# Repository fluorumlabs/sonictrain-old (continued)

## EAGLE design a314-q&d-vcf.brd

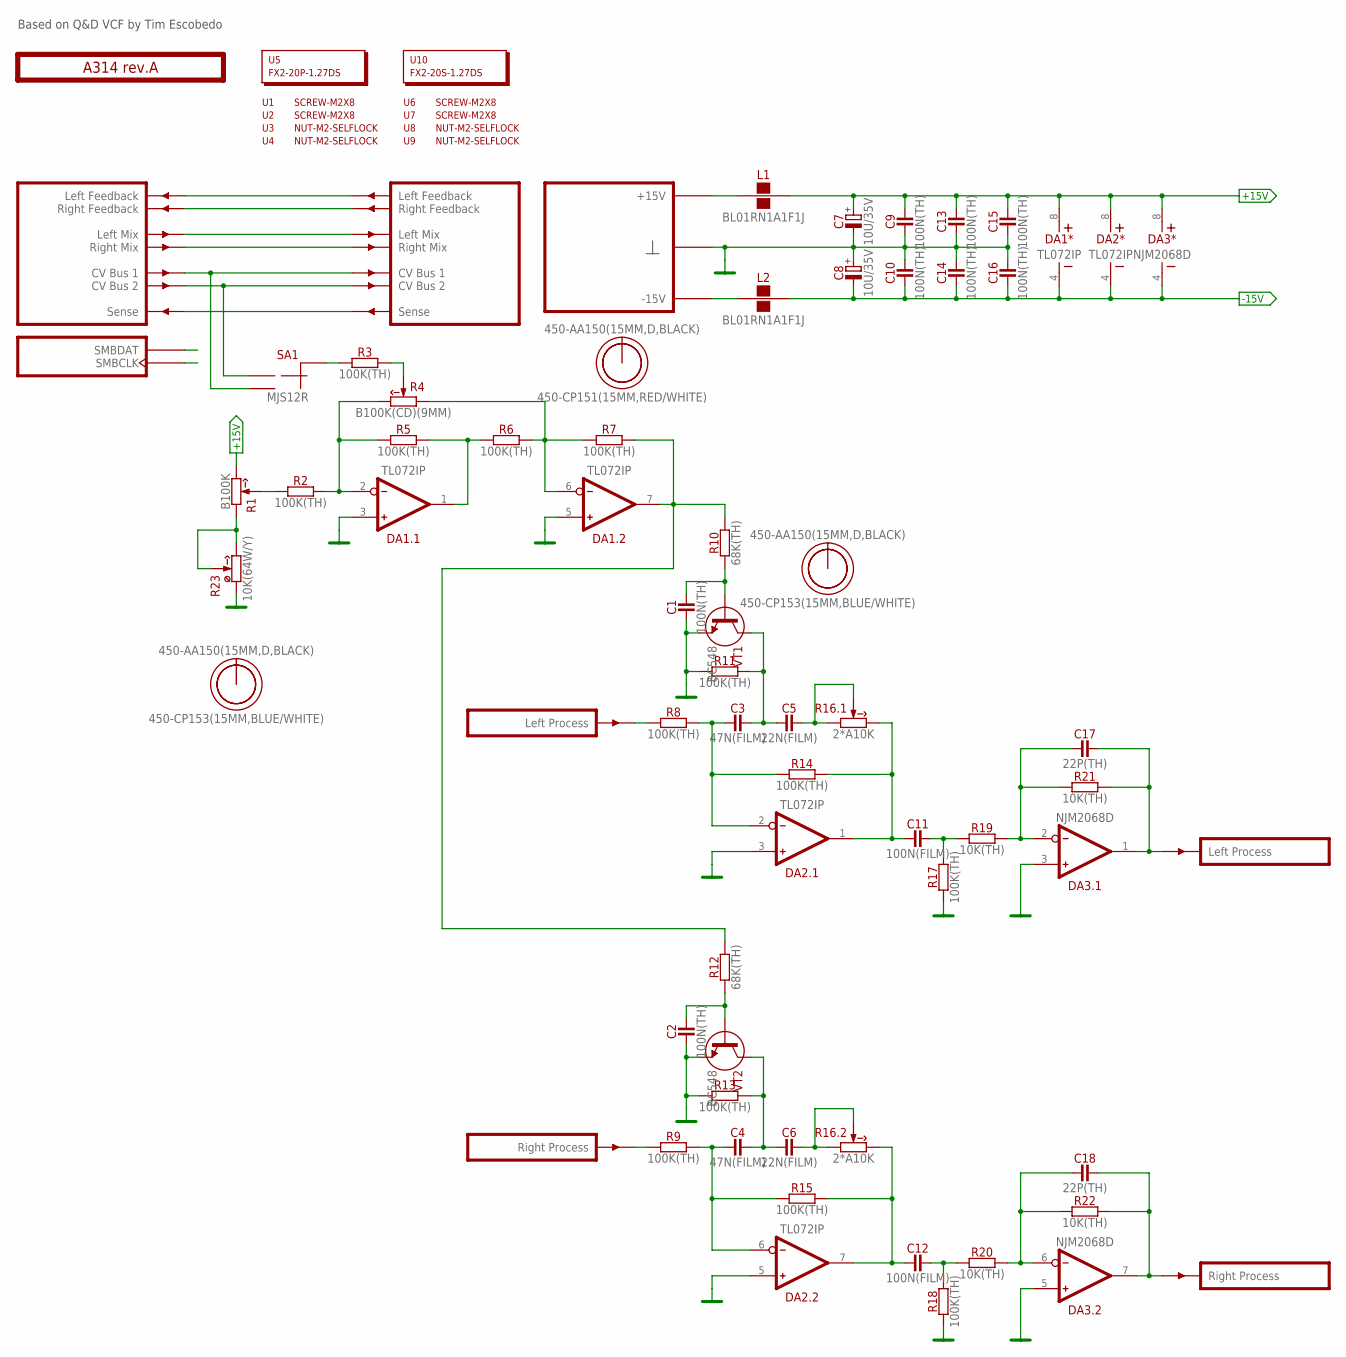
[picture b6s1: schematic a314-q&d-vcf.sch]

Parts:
C1, C2, C9, C10, C13, C14, C15, C16: 100N(TH); C050-024X044
C3, C4: 47N(FILM); C050-025X075
C5, C6: 22N(FILM); C050-025X075
C7, C8: 10U/35V; E2-5
C11, C12: 100N(FILM); C050-025X075
C17, C18: 22P(TH); C050-024X044
DA1, DA2: TL072IP; DIP-8
DA3: NJM2068D; DIP-8
L1, L2: BL01RN1A1F1J; BL01RN1A
O1, O2, O3: 450-AA150(15MM,D,BLACK); EMPTY
O4: 450-CP151(15MM,RED/WHITE); EMPTY
O5, O6: 450-CP153(15MM,BLUE/WHITE); EMPTY
PCB1: A314 rev.A; ST2-BOARD-50
R1: B100K; RV11-SINGLE
R2, R3, R5, R6, R7, R8, R9, R11, R13, R14, R15, R17, R18: 100K(TH); R-0207/10
R4: B100K(CD)(9MM); RV09-SINGLE
R10, R12: 68K(TH); R-0207/10
R16: 2*A10K; RV11-DUAL
R19, R20, R21, R22: 10K(TH); R-0207/10
R23: 10K(64W/Y); 64W
SA1: MJS12R; APEM-MJS12R
U1, U2, U6, U7: SCREW-M2X8; EMPTY
U3, U4, U8, U9: NUT-M2-SELFLOCK; EMPTY
U5: FX2-20P-1.27DS; EMPTY
U10: FX2-20S-1.27DS; EMPTY
VT1, VT2: BC548; TO92

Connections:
+15V: C7.+, C9.2, C13.2, C15.2, DA1.8 (V+), DA2.8 (V+), DA3.8 (V+), L1.2, R1.3 (CW)
-15V: C8.-, C10.1, C14.1, C16.1, DA1.4 (V-), DA2.4 (V-), DA3.4 (V-), L2.2
GND: C1.1, C2.1, C7.-, C8.+, C9.1, C10.2, C13.1, C14.2, C15.1, C16.2, DA1.3 (IN+), DA1.5 (IN+), DA2.3 (IN+), DA2.5 (IN+), DA3.3 (IN+), DA3.5 (IN+), PCB1.B4 (GND), PCB1.B4' (GND), PCB1.B5 (GND), PCB1.B5' (GND), PCB1.B6 (GND), PCB1.B6' (GND), PCB1.B7 (GND), PCB1.B7' (GND), PCB1.B8 (GND), PCB1.B8' (GND), R11.1, R13.1, R17.1, R18.1, R23.1 (CCW), VT1.3 (E), VT2.3 (E)
LMIX: PCB1.ALMIX (LMIX), PCB1.ALMIX' (LMIX')
unnamed: L1.1, PCB1.A+15 (P+15V), PCB1.A+15' (P+15V), PCB1.B+15 (P+15V), PCB1.B+15' (P+15V)
unnamed: PCB1.ALFBK (LFBK), PCB1.ALFBK' (LFBK')
unnamed: R3.2, R4.2 (W)
unnamed: PCB1.ARFBK (RFBK), PCB1.ARFBK' (RFBK')
unnamed: DA1.2 (IN-), R2.2, R4.3 (CW), R5.1
unnamed: DA1.1 (OUT), R5.2, R6.1
unnamed: DA1.6 (IN-), R4.1 (CCW), R6.2, R7.1
unnamed: C18.1, DA3.6 (IN-), R20.2, R22.1
unnamed: R3.1, SA1.C (CM)
unnamed: C4.1, DA2.6 (IN-), R9.2, R15.1
unnamed: C3.1, DA2.2 (IN-), R8.2, R14.1
unnamed: PCB1.BINL (INL), R8.1
unnamed: R1.2 (W), R2.1
unnamed: C11.1, DA2.1 (OUT), R14.2, R16.3 (CW)
unnamed: PCB1.ACV1 (CV1), PCB1.ACV1' (CV1'), SA1.NO (2)
unnamed: PCB1.BSENSE (SENSE), PCB1.BSENSE' (SENSE')
unnamed: C11.2, R17.2, R19.1
unnamed: C12.1, DA2.7 (OUT), R15.2, R16.3' (CW)
unnamed: C5.2, R16.1 (CCW), R16.2 (W)
unnamed: C12.2, R18.2, R20.1
unnamed: C6.2, R16.1' (CCW), R16.2' (W)
unnamed: C3.2, C5.1, R11.2, VT1.1 (C)
unnamed: C1.2, R10.1, VT1.2 (B)
unnamed: C4.2, C6.1, R13.2, VT2.1 (C)
unnamed: L2.1, PCB1.A-15 (P-15V), PCB1.A-15' (P-15V), PCB1.B-15 (P-15V), PCB1.B-15' (P-15V)
unnamed: C2.2, R12.1, VT2.2 (B)
unnamed: PCB1.BINR (INR), R9.1
unnamed: DA1.7 (OUT), R7.2, R10.2, R12.2
unnamed: C18.2, DA3.7 (OUT), PCB1.BOUTR' (OUTR), R22.2
unnamed: C17.1, DA3.2 (IN-), R19.2, R21.1
unnamed: C17.2, DA3.1 (OUT), PCB1.BOUTL' (OUTL), R21.2
unnamed: R1.1 (CCW), R23.3 (CW), R23.S (W), R23.S@1 (W)
unnamed: PCB1.ASMBDAT (SMBDAT), PCB1.ASMBDAT' (SMBDAT)
unnamed: PCB1.ACV2 (CV2), PCB1.ACV2' (CV2'), SA1.NC (1)
unnamed: PCB1.ASMBCLK (SMBCLK), PCB1.ASMBCLK' (SMBCLK)
RMIX: PCB1.ARMIX (RMIX), PCB1.ARMIX' (RMIX')

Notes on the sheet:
Based on Q&D VCF by Tim Escobedo

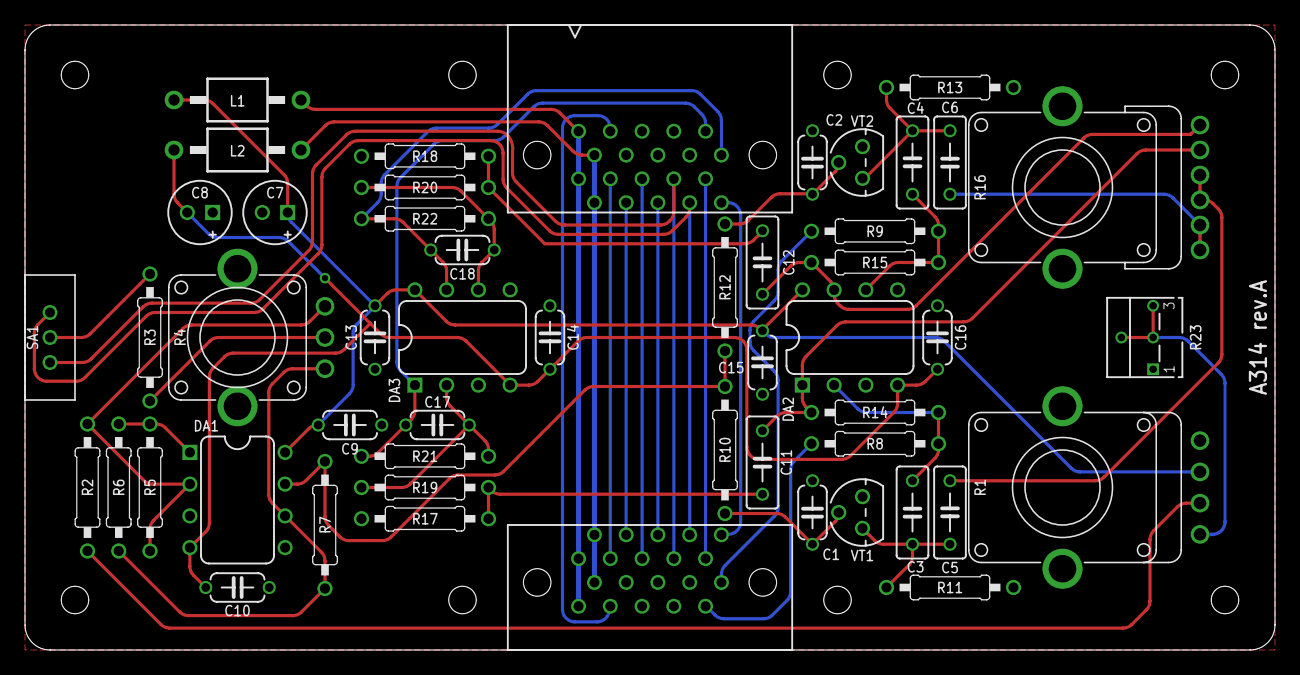
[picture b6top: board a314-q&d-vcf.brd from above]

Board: 2 copper layers, 100.0 x 50.0 mm, 66 parts (0 on the bottom side), 40 nets.

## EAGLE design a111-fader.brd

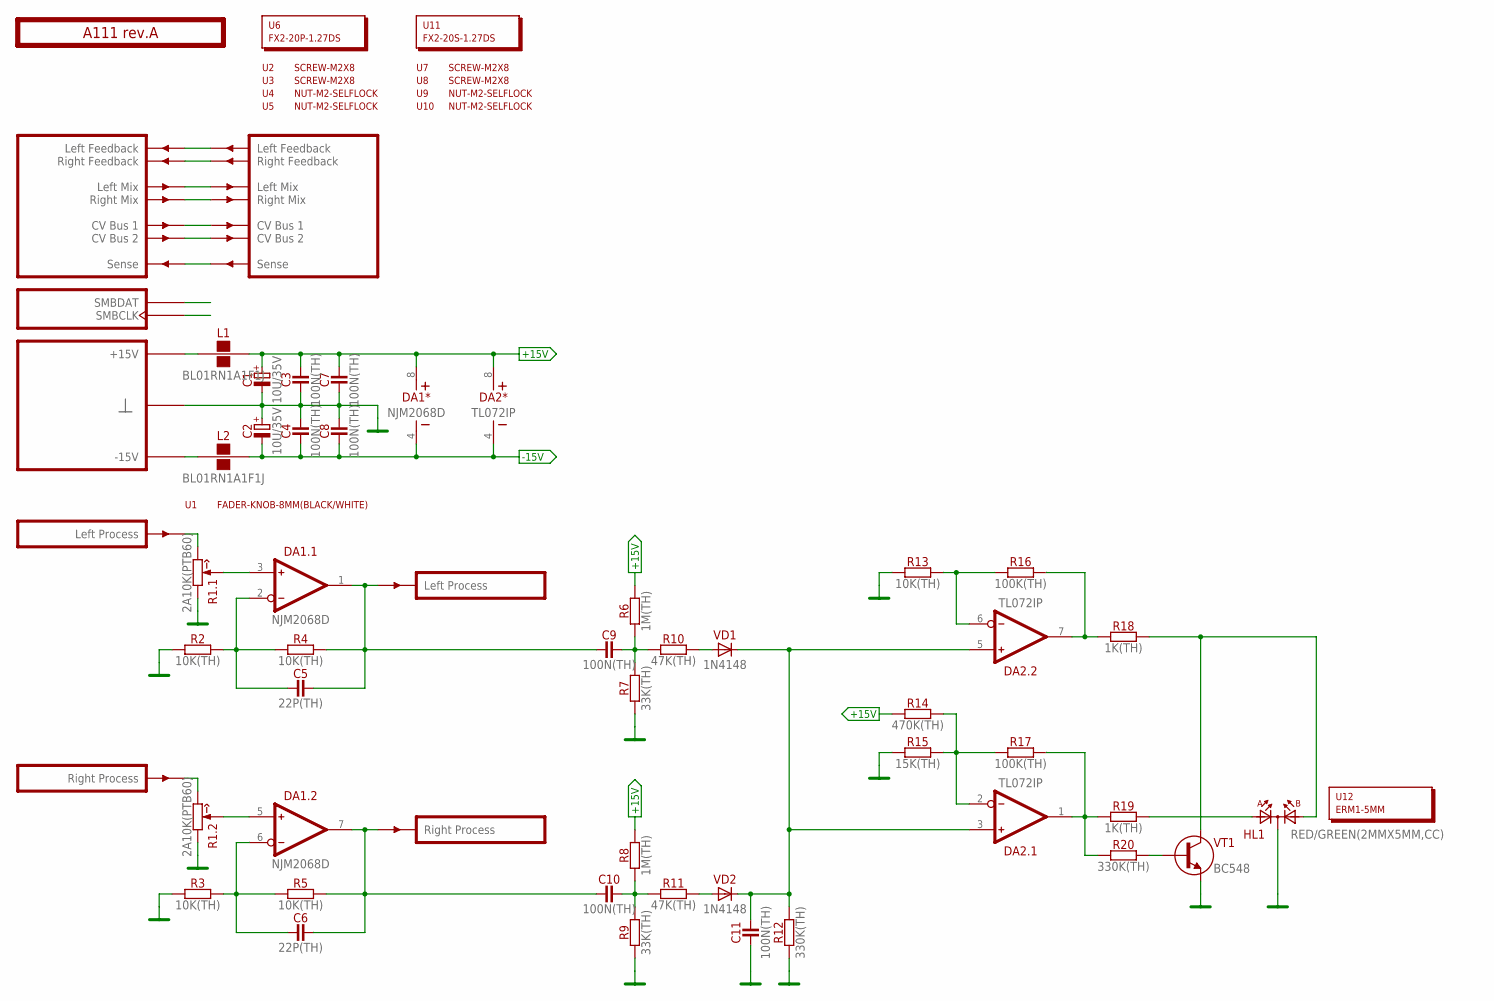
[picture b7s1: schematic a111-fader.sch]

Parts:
C1, C2: 10U/35V; E2-5
C3, C4, C7, C8, C9, C10, C11: 100N(TH); C050-024X044
C5, C6: 22P(TH); C050-024X044
DA1: NJM2068D; DIP-8
DA2: TL072IP; DIP-8
HL1: RED/GREEN(2MMX5MM,CC); LED2X5-3PIN
L1, L2: BL01RN1A1F1J; BL01RN1A
PCB1: A111 rev.A; ST2-BOARD-50
R1: 2A10K(PTB60); PTB6044
R2, R3, R4, R5, R13: 10K(TH); R-0207/10
R6, R8: 1M(TH); R-0207/10
R7, R9: 33K(TH); R-0207/10
R10, R11: 47K(TH); R-0207/10
R12, R20: 330K(TH); R-0207/10
R14: 470K(TH); R-0207/10
R15: 15K(TH); R-0207/10
R16, R17: 100K(TH); R-0207/10
R18, R19: 1K(TH); R-0207/10
U1: FADER-KNOB-8MM(BLACK/WHITE); EMPTY
U2, U3, U7, U8: SCREW-M2X8; EMPTY
U4, U5, U9, U10: NUT-M2-SELFLOCK; EMPTY
U6: FX2-20P-1.27DS; EMPTY
U11: FX2-20S-1.27DS; EMPTY
U12: ERM1-5MM; EMPTY
VD1, VD2: 1N4148; DO35-7
VT1: BC548; TO92

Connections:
+15V: C1.+, C3.2, C7.2, DA1.8 (V+), DA2.8 (V+), L1.2, R6.2, R8.2, R14.1
-15V: C2.-, C4.1, C8.1, DA1.4 (V-), DA2.4 (V-), L2.2
GND: C1.-, C2.+, C3.1, C4.2, C7.1, C8.2, C11.1, HL1.K, PCB1.B4 (GND), PCB1.B4' (GND), PCB1.B5 (GND), PCB1.B5' (GND), PCB1.B6 (GND), PCB1.B6' (GND), PCB1.B7 (GND), PCB1.B7' (GND), PCB1.B8 (GND), PCB1.B8' (GND), R1.A1 (CCW), R1.B1 (CCW), R2.1, R3.1, R7.1, R9.1, R12.1, R13.1, R15.1, VT1.3 (E)
unnamed: PCB1.ALFBK (LFBK), PCB1.ALFBK' (LFBK')
unnamed: PCB1.ARFBK (RFBK), PCB1.ARFBK' (RFBK')
unnamed: PCB1.ALMIX (LMIX), PCB1.ALMIX' (LMIX')
unnamed: PCB1.ARMIX (RMIX), PCB1.ARMIX' (RMIX')
unnamed: PCB1.ACV1 (CV1), PCB1.ACV1' (CV1')
unnamed: PCB1.ACV2 (CV2), PCB1.ACV2' (CV2')
unnamed: PCB1.BSENSE (SENSE), PCB1.BSENSE' (SENSE')
unnamed: PCB1.ASMBDAT (SMBDAT), PCB1.ASMBDAT' (SMBDAT)
unnamed: PCB1.ASMBCLK (SMBCLK), PCB1.ASMBCLK' (SMBCLK)
unnamed: PCB1.BINL (INL), R1.A3 (CW)
unnamed: DA1.3 (IN+), R1.A2 (W)
unnamed: C5.1, DA1.2 (IN-), R2.2, R4.1
unnamed: DA2.6 (IN-), R13.2, R16.1
unnamed: PCB1.BINR (INR), R1.B3 (CW)
unnamed: DA1.5 (IN+), R1.B2 (W)
unnamed: C6.1, DA1.6 (IN-), R3.2, R5.1
unnamed: DA2.7 (OUT), R16.2, R18.1
unnamed: C6.2, C10.1, DA1.7 (OUT), PCB1.BOUTR' (OUTR), R5.2
unnamed: C5.2, C9.1, DA1.1 (OUT), PCB1.BOUTL' (OUTL), R4.2
unnamed: C9.2, R6.1, R7.2, R10.1
unnamed: R10.2, VD1.A
unnamed: C10.2, R8.1, R9.2, R11.1
unnamed: R11.2, VD2.A
unnamed: C11.2, DA2.3 (IN+), DA2.5 (IN+), R12.2, VD1.C, VD2.C
unnamed: L1.1, PCB1.A+15 (P+15V), PCB1.A+15' (P+15V), PCB1.B+15 (P+15V), PCB1.B+15' (P+15V)
unnamed: HL1.A2, R18.2, VT1.1 (C)
unnamed: DA2.2 (IN-), R14.2, R15.2, R17.1
unnamed: DA2.1 (OUT), R17.2, R19.1, R20.1
unnamed: R20.2, VT1.2 (B)
unnamed: HL1.A1, R19.2
unnamed: L2.1, PCB1.A-15 (P-15V), PCB1.A-15' (P-15V), PCB1.B-15 (P-15V), PCB1.B-15' (P-15V)

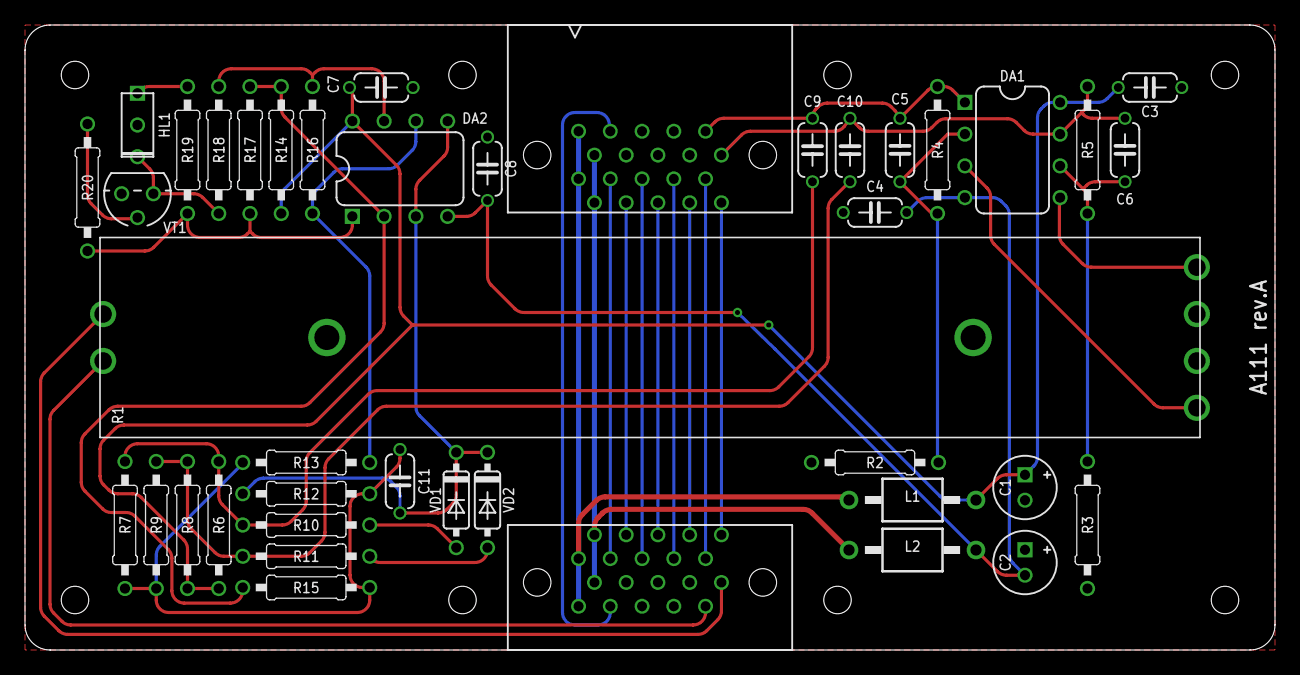
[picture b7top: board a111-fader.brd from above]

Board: 2 copper layers, 100.0 x 50.0 mm, 52 parts (0 on the bottom side), 34 nets.

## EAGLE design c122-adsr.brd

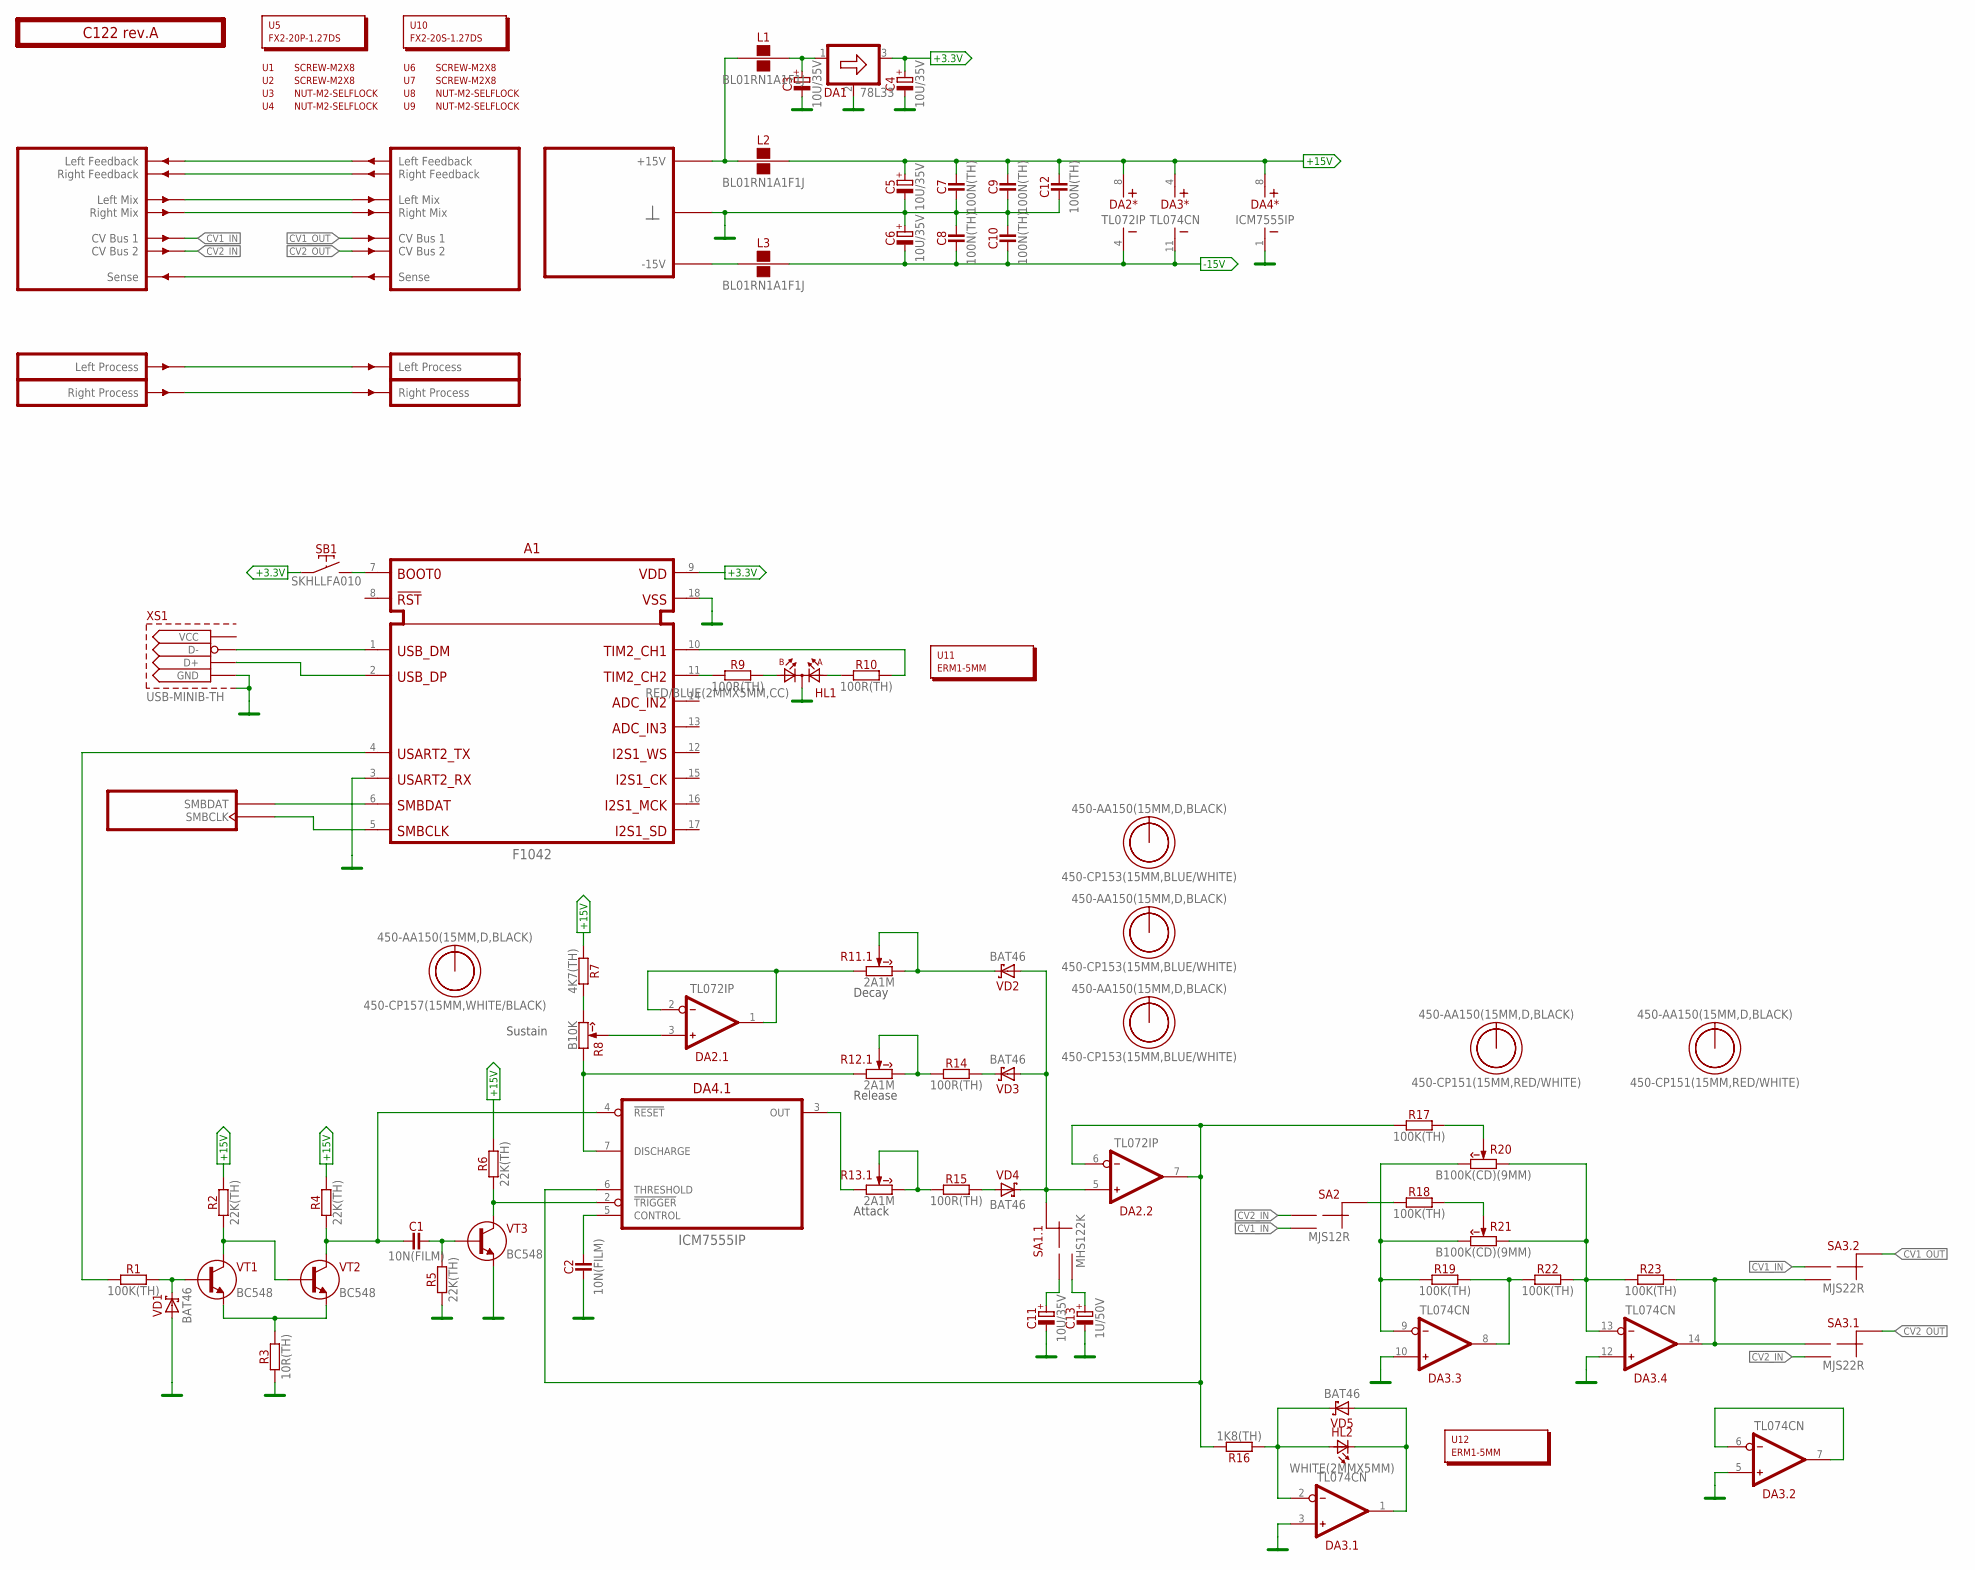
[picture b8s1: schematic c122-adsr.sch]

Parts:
A1: F1042; F-DIP18
C1, C2: 10N(FILM); C050-025X075
C3, C4, C5, C6, C11: 10U/35V; E2-5
C7, C8, C9, C10, C12: 100N(TH); C050-024X044
C13: 1U/50V; E1,5-4
DA1: 78L33; TO92
DA2: TL072IP; DIP-8
DA3: TL074CN; DIP-14
DA4: ICM7555IP; DIP-8
HL1: RED/BLUE(2MMX5MM,CC); LED2X5-3PIN
HL2: WHITE(2MMX5MM); LED2X5
L1, L2, L3: BL01RN1A1F1J; BL01RN1A
O1, O3, O5, O7, O9, O11: 450-AA150(15MM,D,BLACK); EMPTY
O2: 450-CP157(15MM,WHITE/BLACK); EMPTY
O4, O6, O8: 450-CP153(15MM,BLUE/WHITE); EMPTY
O10, O12: 450-CP151(15MM,RED/WHITE); EMPTY
PCB1: C122 rev.A; ST2-BOARD-74
R1, R17, R18, R19, R22, R23: 100K(TH); R-0207/10
R2, R4, R5, R6: 22K(TH); R-0207/10
R3: 10R(TH); R-0207/10
R7: 4K7(TH); R-0207/10
R8: B10K; RV11-SINGLE
R9, R10, R14, R15: 100R(TH); R-0207/10
R11, R12, R13: 2A1M; RV11-DUAL
R16: 1K8(TH); R-0207/10
R20, R21: B100K(CD)(9MM); RV09-SINGLE
SA1: MHS122K; APEM-MHS122K
SA2: MJS12R; APEM-MJS12R
SA3: MJS22R; APEM-MJS22R
SB1: SKHLLFA010
U1, U2, U6, U7: SCREW-M2X8; EMPTY
U3, U4, U8, U9: NUT-M2-SELFLOCK; EMPTY
U5: FX2-20P-1.27DS; EMPTY
U10: FX2-20S-1.27DS; EMPTY
U11, U12: ERM1-5MM; EMPTY
VD1, VD2, VD3, VD4, VD5: BAT46; DO35-7
VT1, VT2, VT3: BC548; TO92
XS1: USB-MINIB-TH; USB-MB-H

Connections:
+3.3V: A1.9 (VDD), C4.+, DA1.3 (OUT), SB1.1
+15V: C5.+, C7.2, C9.2, C12.2, DA2.8 (V+), DA3.4 (V+), DA4.8 (V+), L2.2, R2.2, R4.2, R6.2, R7.2
-15V: C6.-, C8.1, C10.1, DA2.4 (V-), DA3.11 (V-), L3.2
CV1_IN: PCB1.ACV1 (CV1), SA2.NO (2), SA3.NC2 (1)
CV1_OUT: PCB1.ACV1' (CV1'), SA3.C2 (CM)
CV2_IN: PCB1.ACV2 (CV2), SA2.NC (1), SA3.NO1 (2)
CV2_OUT: PCB1.ACV2' (CV2'), SA3.C1 (CM)
GND: A1.3 (USART2_RX), A1.18 (VSS), C2.1, C3.-, C4.-, C5.-, C6.+, C7.1, C8.2, C9.1, C10.2, C11.-, C12.1, C13.-, DA1.2 (GND), DA3.3 (IN+), DA3.5 (IN+), DA3.10 (IN+), DA3.12 (IN+), DA4.1 (V-), HL1.K, PCB1.B4 (GND), PCB1.B4' (GND), PCB1.B5 (GND), PCB1.B5' (GND), PCB1.B6 (GND), PCB1.B6' (GND), PCB1.B7 (GND), PCB1.B7' (GND), PCB1.B8 (GND), PCB1.B8' (GND), R3.1, R5.1, VD1.A, VT3.3 (E), XS1.GND, XS1.P$1 (S1), XS1.P$2 (S1), XS1.P$6 (S1), XS1.P$7 (S1)
LMIX: PCB1.ALMIX (LMIX), PCB1.ALMIX' (LMIX')
unnamed: L1.1, L2.1, PCB1.A+15 (P+15V), PCB1.A+15' (P+15V), PCB1.B+15 (P+15V), PCB1.B+15' (P+15V)
unnamed: PCB1.ALFBK (LFBK), PCB1.ALFBK' (LFBK')
unnamed: C3.+, DA1.1 (IN), L1.2
unnamed: PCB1.ARFBK (RFBK), PCB1.ARFBK' (RFBK')
unnamed: A1.11 (TIM2_CH2), R9.1
unnamed: A1.6 (SBMDAT), PCB1.ASMBDAT (SMBDAT), PCB1.ASMBDAT' (SMBDAT)
unnamed: A1.5 (SMBCLK), PCB1.ASMBCLK (SMBCLK), PCB1.ASMBCLK' (SMBCLK)
unnamed: A1.7 (BOOT0), SB1.2
unnamed: A1.1 (USB_DM), XS1.D-
unnamed: PCB1.BINL (INL), PCB1.BOUTL' (OUTL)
unnamed: PCB1.BINR (INR), PCB1.BOUTR' (OUTR)
unnamed: A1.2 (USB_DP), XS1.D+
unnamed: HL1.A2, R9.2
unnamed: HL1.A1, R10.1
unnamed: A1.10 (TIM2_CH1), R10.2
unnamed: PCB1.BSENSE (SENSE), PCB1.BSENSE' (SENSE')
unnamed: DA4.3 (OUT), R13.1 (CCW)
unnamed: R1.2, VD1.C, VT1.2 (B)
unnamed: R3.2, VT1.3 (E), VT2.3 (E)
unnamed: R2.1, VT1.1 (C), VT2.2 (B)
unnamed: C1.1, DA4.4 (!RESET), R4.1, VT2.1 (C)
unnamed: R15.2, VD4.A
unnamed: C1.2, R5.2, VT3.2 (B)
unnamed: DA4.2 (!TRIGGER), R6.1, VT3.1 (C)
unnamed: L3.1, PCB1.A-15 (P-15V), PCB1.A-15' (P-15V), PCB1.B-15 (P-15V), PCB1.B-15' (P-15V)
unnamed: C2.2, DA4.5 (CONTROL)
unnamed: A1.4 (USART2_TX), R1.1
unnamed: DA4.7 (DISCHARGE), R8.1 (CCW), R12.1 (CCW)
unnamed: R7.1, R8.3 (CW)
unnamed: DA2.1 (OUT), DA2.2 (IN-), R11.1 (CCW)
unnamed: DA2.3 (IN+), R8.2 (W)
unnamed: R11.2 (W), R11.3 (CW), VD2.C
unnamed: R12.2 (W), R12.3 (CW), R14.1
unnamed: R13.2 (W), R13.3 (CW), R15.1
unnamed: DA2.5 (IN+), SA1.CMN (CM), VD2.A, VD3.A, VD4.C
unnamed: DA3.2 (IN-), HL2.A, R16.1, VD5.C
unnamed: R18.2, R21.2 (W)
unnamed: R14.2, VD3.C
unnamed: C11.+, SA1.1
unnamed: DA3.1 (OUT), HL2.K (C), VD5.A
unnamed: DA3.9 (IN-), R19.1, R20.3 (CW), R21.3 (CW)
unnamed: C13.+, SA1.2
unnamed: DA3.8 (OUT), R19.2, R22.1
unnamed: DA3.13 (IN-), R20.1 (CCW), R21.1 (CCW), R22.2, R23.1
unnamed: DA3.14 (OUT), R23.2, SA3.NC1 (1), SA3.NO2 (2)
unnamed: R18.1, SA2.C (CM)
unnamed: R17.2, R20.2 (W)
unnamed: DA2.6 (IN-), DA2.7 (OUT), DA4.6 (THRESHOLD), R16.2, R17.1
unnamed: DA3.6 (IN-), DA3.7 (OUT)
RMIX: PCB1.ARMIX (RMIX), PCB1.ARMIX' (RMIX')

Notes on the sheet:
Sustain
Decay
Release
Attack

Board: 2 copper layers, 84 parts (0 on the bottom side), 59 nets, no tracks yet.

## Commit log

2015-11-15 Initial commit
    + M2101 - PSU DC/DC
    + M2201 - Stereo Input
    + M2301 - Stereo Output
2015-11-15 Add (dummy) FX2 connectors to sch
2015-11-15 Add CERN Open Hardware License v1.2
2015-11-15 Add README
2015-11-25 D2101 initial commit
2015-11-25 Fix PJ-051AH pinout (#1)
2015-11-25 Board rev.A -> rev.B
2015-11-25 Add Z00001, Z00002, Z00003-5, M21012 and M21013-5 panels
2015-11-25 Add w120-6045 panel (D-shaft spacer)
2015-11-25 Add M21016 panels with switch and without switch
2015-11-26 Fix module name position
2015-11-27 Add Gitter badge
2015-11-27 Fix README.md formatting
2015-12-01 D2101 done
2015-12-04 Replace switchable delay potentiometers with single ones
2015-12-04 Minor routing adjustment
2015-12-04 Signal indicator refactoring (#5) + no noise when no jack inserted (#6)
2015-12-04 Mouser part number fix
2015-12-04 Change headphone amplifier gain to +15 dB #4
2015-12-04 Renumber components
2015-12-08 m2301 PCB update
2015-12-08 Replace 10R resistors with ferrite beads Replace 47u/35V with 33u/25V
2015-12-08 Replace 10R with ferrite bead Replace 47u/35V with 33u/25V
2015-12-08 a2401 Diode Distortion schematic
2015-12-08 a2402 4069 distortion schematic
2015-12-10 Replaced bypass switch with blend potentiometer
2015-12-13 a2402 rename
2015-12-13 a2402 routing
2015-12-13 Replace feedback switch with MJS22R
2015-12-14 d2101 controls placement fix
2015-12-14 d2102 SpinSemi FX Board
2015-12-14 Changed 47u/16V -> 10u/35V
2015-12-14 a2401 diode distortion board
2015-12-16 m901 vu meter schematic and routing
2015-12-16 a2401 -> a401 rename
2015-12-16 a2402 -> a402 rename
2015-12-16 d2101 -> d101 rename
2015-12-16 d2102 -> d102 rename
2015-12-16 m2301 -> m301 rename
2015-12-22 d701 initial design
2015-12-23 d701 routing update
2016-03-01 M2201 -> M201 Rename
2016-03-01 M201 In T/H
2016-03-02 M301 Update
2016-03-02 M301 Routing
2016-03-02 A202 4Band EQ Schematics and Board
2016-03-03 A202 Routing Update
2016-03-03 A101 Fader Schematic and Board
2016-03-03 A201 WIP
2016-03-03 Add Potentiometer Knobs
2016-03-03 Add Knobs
2016-03-04 A201 Routing Update
2016-03-04 Module Footprint Update
2016-03-04 D101 Update
2016-03-06 PCB Update
2016-03-06 M201 -> M202
2016-03-06 A401 -> A405
2016-03-06 M301 -> M303
2016-03-06 A101 -> A111
2016-03-06 A201 -> A212
2016-03-06 A202 -> A210
2016-03-06 A402 -> A410
2016-03-06 D701 -> D709
2016-03-06 D101 -> D104
2016-03-06 D102 -> D108
2016-03-06 M901 -> M907
2016-03-06 PSU PCB Update
2016-03-06 M2101 -> M101
2016-03-06 A410 -> A406
2016-03-06 A405 Update
2016-03-07 Add ZZ050 and ZM101
2016-03-07 Remove old panels
2016-03-07 Add ZM101-HP
2016-03-07 ZM101-HP Update
2016-03-09 M913 Dev Adapter PCB & Schematics
2016-03-09 M913b Breadboard
2016-03-09 Add missing female connectors
2016-03-09 Misc. component update
2016-03-09 Add ERM1-4MM for LEDs
2016-03-09 M913 Component Values Update
2016-03-10 A406 in T/H
2016-03-11 Add ZA210, ZA212, ZA405, ZA406, ZD104, ZD709, ZM202 and ZM303 panels
2016-03-14 Fix M913b Board
2016-03-14 Fix copyright positioning
2016-04-01 D709 Update to use F1042
2016-04-01 A314 Q&D VCF Preliminary
2016-04-04 A314 Prototyping in progress
2016-04-04 Enclosure drawings update
2016-04-04 A111 Update max gain to +10 instead of +6
2016-04-04 Add ZM913, ZM907, ZD108, ZA111
2016-04-04 Add ZZ026
2016-04-06 D104 Knobs update
2016-04-07 Add CV knob
2016-04-19 A314 Schematic and PCB
2016-04-19 A314 Add knobs
2016-04-19 A314 Add trimmer to set cutoff range
2016-04-20 A314 Routing correction
2016-05-18 M101 rev.C Initial Schematic
2016-05-18 M101 Parts renumbering
2016-05-19 A915 Initial Schematics
2016-05-20 C116 Initial Schematics
2016-05-20 A917 Initial Schematic
2016-05-24 A718 Initial Schematics
2016-05-24 A718 Update
2016-05-24 A718 Fix Feedback
2016-05-24 M219 Initial Schematics
2016-05-24 A320 Initial Schematics
2016-05-25 M921 Initial Schematics
2016-05-26 C116 Update
2016-05-26 C122 Initial Schematics
2016-05-26 C116 LED circuit update
2016-05-26 M219 LED Color Update
2016-05-27 A323 Initial Schematic
2016-05-28 A323 TH Version
2016-05-28 A323 PCB Update
2016-05-30 A323 Opamps update
2016-05-30 A323 Update to LM13700
2016-05-31 A124 Initial Schematics
2016-05-31 A323 Module rename
2016-05-31 A124 Update
2016-06-01 D725 Initial Schematics
2016-06-02 BC558 -> BC556 Update
2016-06-02 M907 LED VU color update
2016-06-06 M907: Change 100R to 180R
2016-06-08 A111 New VU Indicator preliminary
2016-06-08 M101 Polarity Protection Fix
2016-06-09 M101c Update
2016-06-10 M101c: Routing
2016-06-10 A111a Routing
2016-06-10 M202d: Improved signal indicator
2016-06-10 M202d: Resistor values fix
2016-06-11 M303 rev.D: Updated signal indicator
2016-06-11 M921 Updated signal indicator
2016-06-11 M303d Resistor Value Update
2016-06-11 M202d Resistor Value Update
2016-06-11 A111a: Resistor Value Update
2016-06-11 D709 LED Color Change
2016-06-11 D725 LED Color Change
2016-06-11 C122a LED Color Change
2016-06-20 A111 Change resistor positioning to better tolerate 0207 resistors
2016-06-20 A111 Silkscreen update
2016-06-20 A915a Change component placement
2016-06-27 A314 Resistor placement adjustment
2016-07-18 M219a Routing
2016-07-18 A915a Routing
2016-07-18 A917 Routing
2016-07-18 A718a Routing
2016-07-19 M101d Schematic/Routing Update
2020-12-02 Add .whitesource configuration file
